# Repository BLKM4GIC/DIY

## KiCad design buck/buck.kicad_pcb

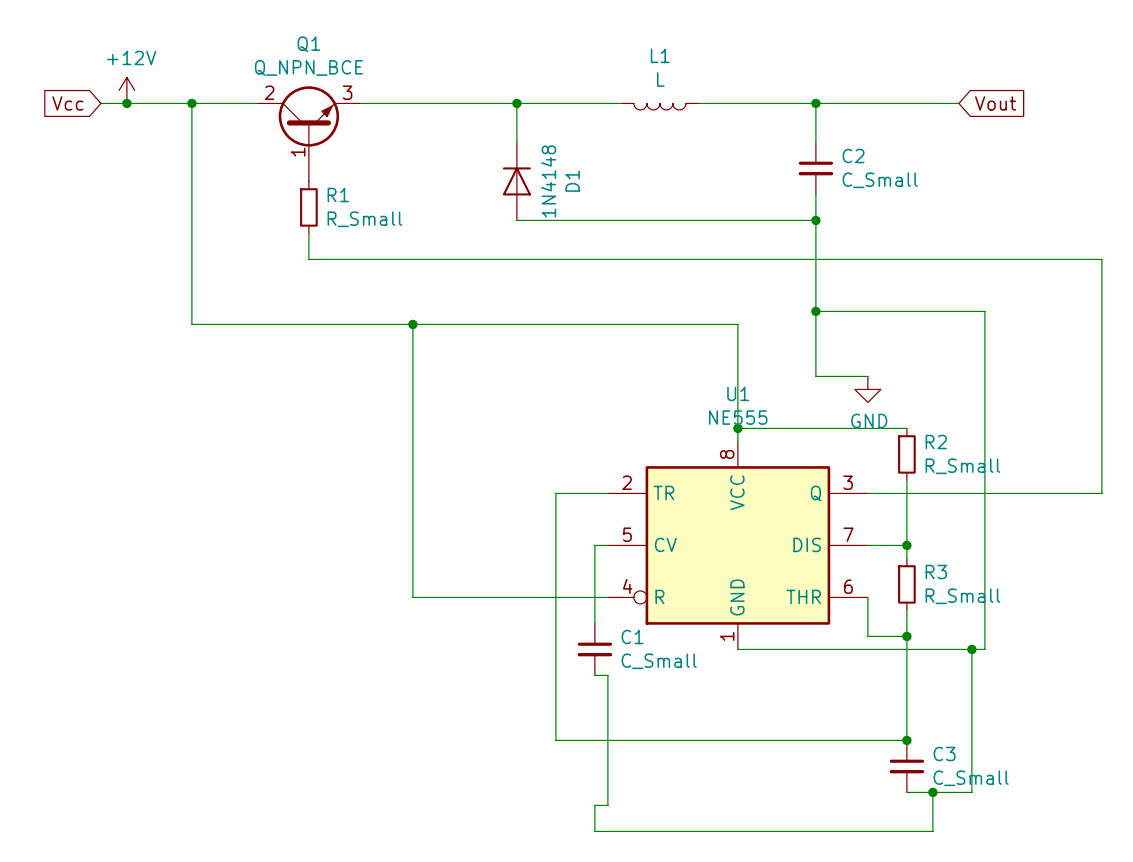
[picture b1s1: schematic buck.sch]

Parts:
C1: C_Small; C_Disc_D3.0mm_W1.6mm_P2.50mm
C2: C_Small; C_0805_2012Metric
C3: C_Small; C_0402_1005Metric
D1: 1N4148; D_DO-35_SOD27_P7.62mm_Horizontal
L1: L; L_Radial_D9.5mm_P5.00mm_Fastron_07HVP
Q1: Q_NPN_BCE; TO-3P-3_Vertical
R1, R2, R3: R_Small; R_Axial_DIN0204_L3.6mm_D1.6mm_P5.08mm_Vertical
U1: NE555; DIP-8_W7.62mm_LongPads

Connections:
GND: C1.2, C2.2, C3.2, D1.2 (A), U1.1 (GND)
unnamed: C1.1, U1.5 (CV)
unnamed: C3.1, R3.2, U1.2 (TR), U1.6 (THR)
unnamed: D1.1 (K), L1.2, Q1.3 (E)
unnamed: Q1.1 (B), R1.1
unnamed: R1.2, U1.3 (Q)
unnamed: R2.2, R3.1, U1.7 (DIS)
Vcc: Q1.2 (C), R2.1, U1.4 (R), U1.8 (VCC)
Vout: C2.1, L1.1

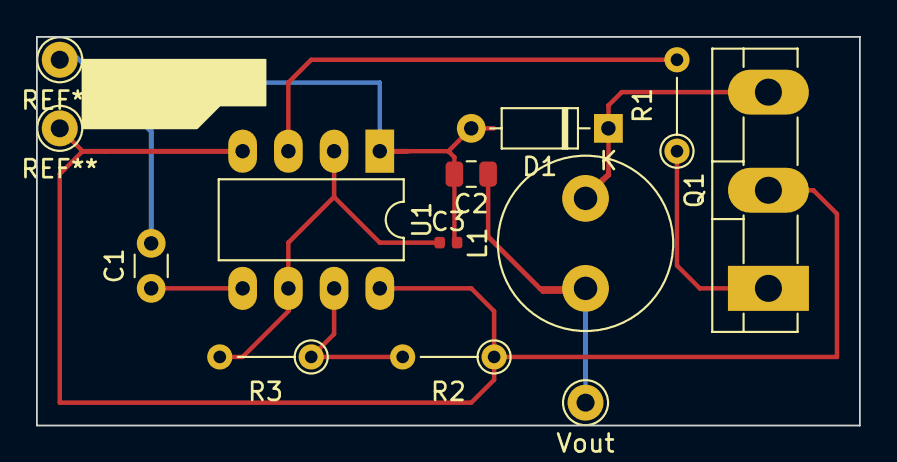
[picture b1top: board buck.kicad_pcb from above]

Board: 2 copper layers, 45.7 x 21.6 mm, 11 parts (0 on the bottom side), 9 nets.

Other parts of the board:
Vout: Pin_D1.0mm_L10.0mm
